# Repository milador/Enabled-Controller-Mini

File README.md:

# Enabled-Controller-Mini

Enabled Controller Mini is a more affordable version of <a href="https://github.com/milador/Enabled-Controller">Enabled-Controller</a> which is an open-source switch controller interface that enables those with limited or no hand movement to use Adaptive switches as input to operate and perform joystick actions.

The device offers up to four switch input enclosures through four 3.5mm audio jacks and two analog inputs through one 3.5mm headphone jack. The one 3.5mm headphone jacks can be used to connect one X-Y analog joystick.

The internal RGB led of QT Py board is used to provide visual feedback for each action.

## Assembly Instructions Manual

The <a href="https://github.com/milador/Enabled-Controller-Mini/blob/main/Documentation/Build_Manuals/Enabled_Controller_Mini_Instructions_Manual.pdf">Assembly Instructions Manual</a> is available to download.

## Parts

The <a href="https://github.com/milador/Enabled-Controller-Mini/blob/main/Components/Enabled_Controller_Mini_BOM.csv">BOM</a> file is available to download.

## Software

The first experimental software is under testing.

## Hardware 

### PCB Design 

The <a href="https://github.com/milador/Enabled-Controller-Mini/tree/main/Hardware/PCB">PCB files</a> including both PCB Eagle design files and generated gerber files are available to download.

### Enclosure

The <a href="https://github.com/milador/Enabled-Controller-Mini/tree/main/Hardware/Enclosure">Enclosure files</a> including both STL and STEP enclosure files are available to download.

## License

### Creative Commons Attribution-NonCommercial-ShareAlike (CC-BY-NC-SA)

Copyright (c) 2021 Milador

A creative commons license that bans commercial use and requires you to release any modified works under this license.

<br />This work is licensed under a <a rel="license" href="http://creativecommons.org/licenses/by-nc-sa/3.0/">Creative Commons Attribution-NonCommercial-ShareAlike 3.0 Unported License</a>.

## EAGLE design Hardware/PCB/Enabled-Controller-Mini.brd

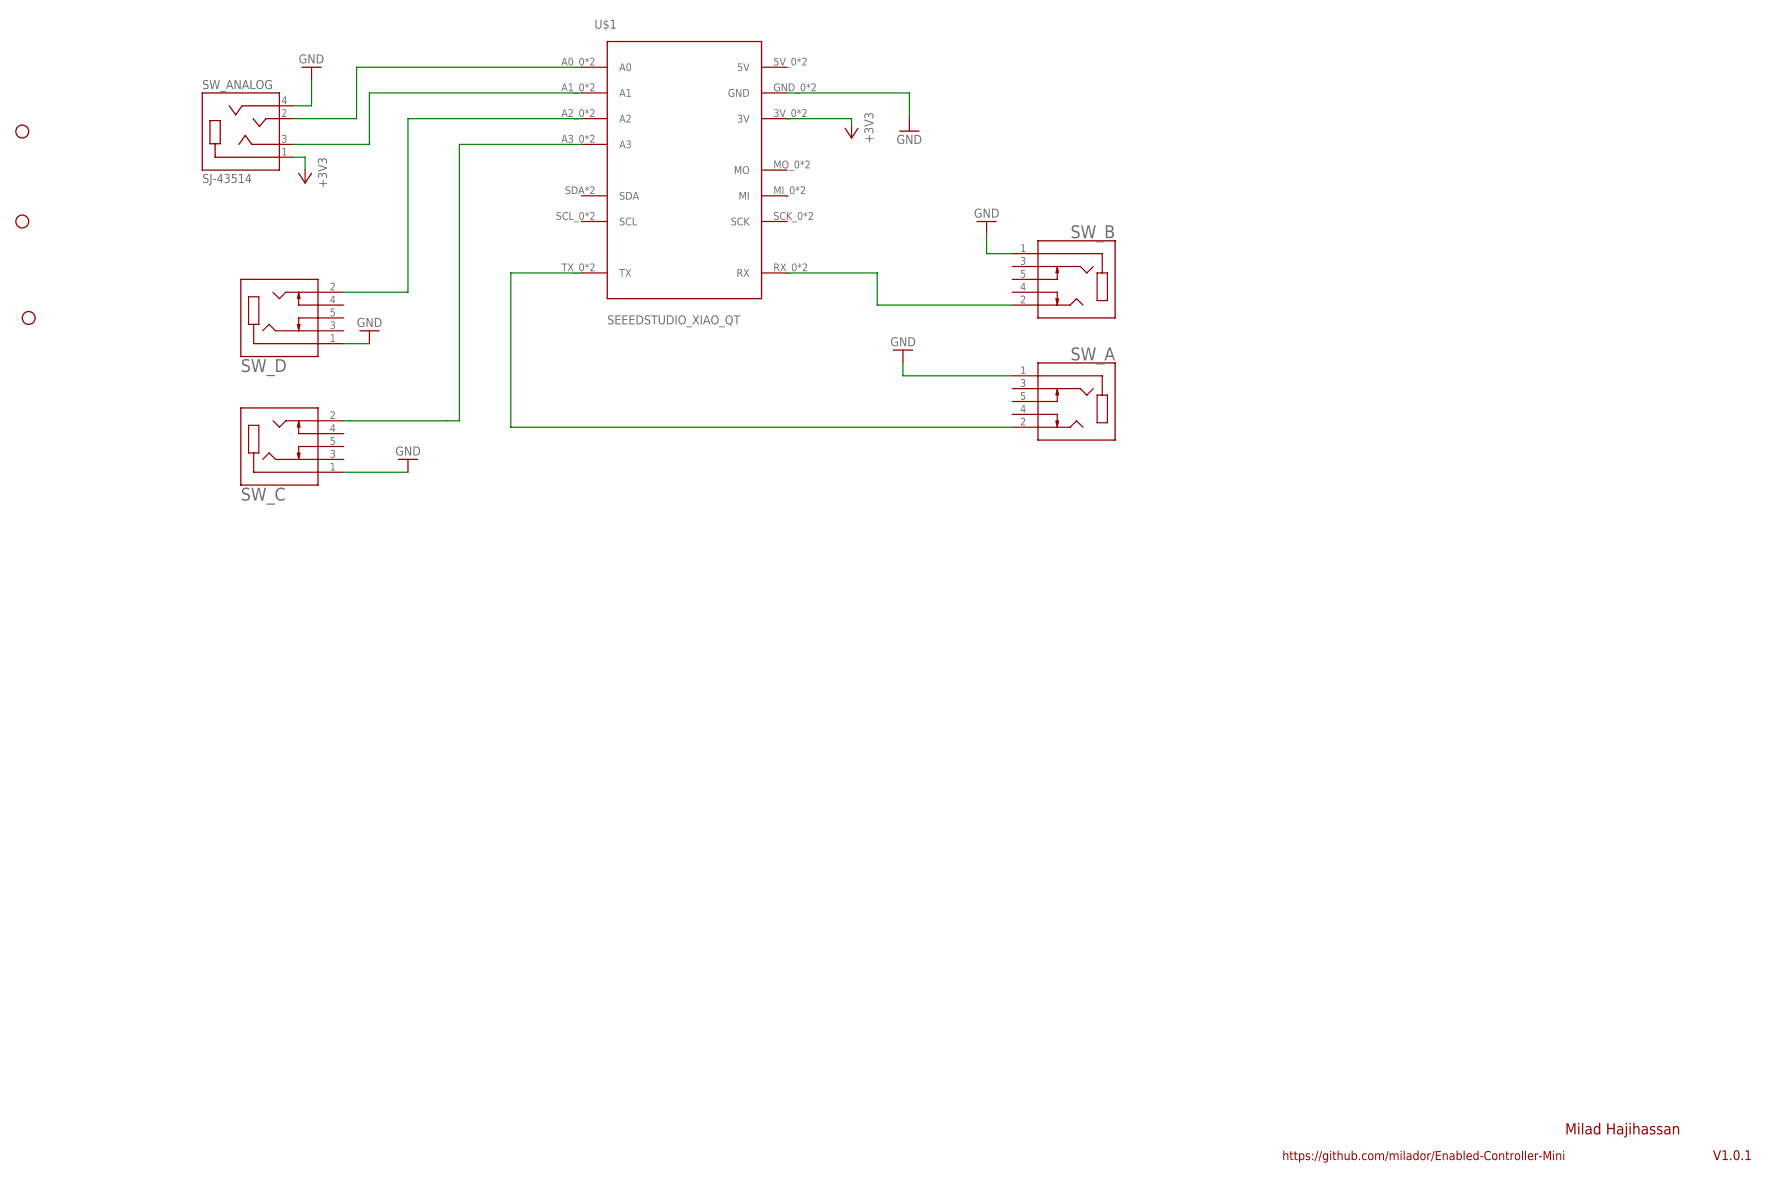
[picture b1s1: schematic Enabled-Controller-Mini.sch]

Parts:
STANDOFF1, STANDOFF2, STANDOFF3: STAND-OFF-; STAND-OFF
SW_A: CUI_SJ1-3535NGSJ1-3535NG; CUI_SJ1-3535NG
SW_ANALOG: SJ-43514; CUI_SJ-43514
SW_B: CUI_SJ1-3535NGSJ1-3535NG; CUI_SJ1-3535NG
SW_C: CUI_SJ1-3535NGSJ1-3535NG; CUI_SJ1-3535NG
SW_D: CUI_SJ1-3535NGSJ1-3535NG; CUI_SJ1-3535NG
U$1: SEEEDSTUDIO_XIAO_QT; SEEEDSTUDIO_XIAO

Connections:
+3V3: SW_ANALOG.1 (SLEEVE), U$1.3V_0 (3V), U$1.3V_1 (3V)
GND: SW_A.1, SW_ANALOG.4 (RING2), SW_B.1, SW_C.1, SW_D.1, U$1.GND_0 (GND), U$1.GND_1 (GND)
unnamed: SW_B.2, U$1.RX_0 (RX), U$1.RX_1 (RX)
unnamed: SW_A.2, U$1.TX_0 (TX), U$1.TX_1 (TX)
unnamed: SW_ANALOG.2 (TIP), U$1.A0_0 (A0), U$1.A0_1 (A0)
unnamed: SW_C.2, U$1.A3_0 (A3), U$1.A3_1 (A3)
unnamed: SW_ANALOG.3 (RING1), U$1.A1_0 (A1), U$1.A1_1 (A1)
unnamed: SW_D.2, U$1.A2_0 (A2), U$1.A2_1 (A2)

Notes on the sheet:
V1.0.1
Milad Hajihassan
https://github.com/milador/Enabled-Controller-Mini

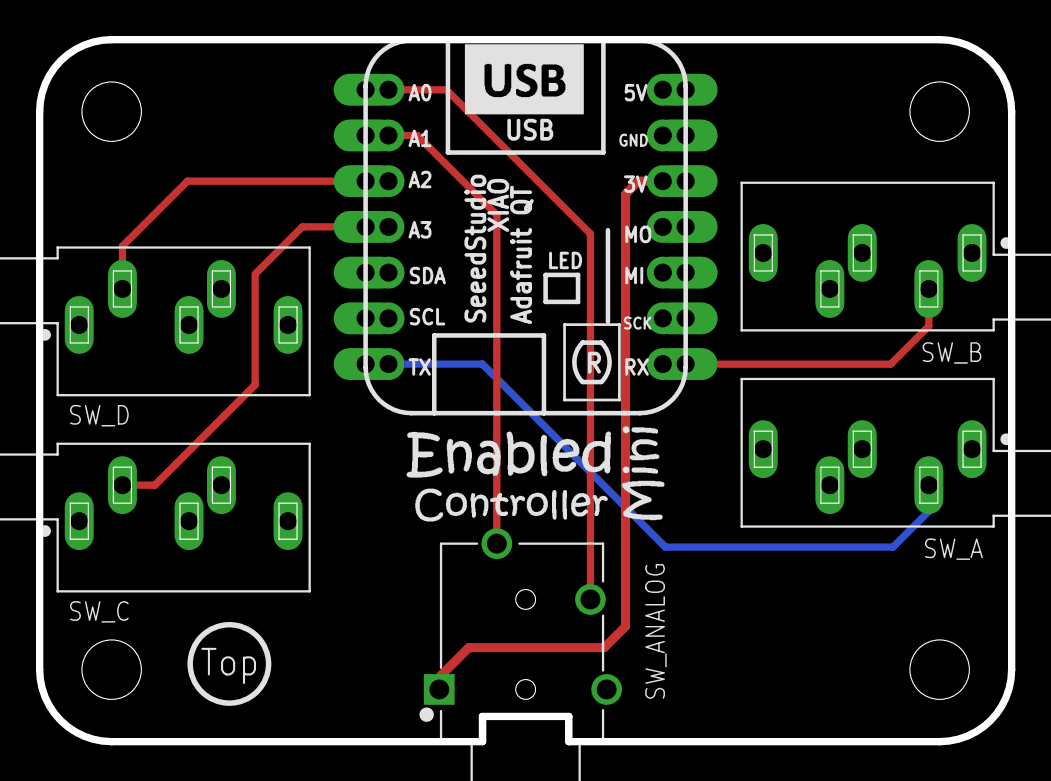
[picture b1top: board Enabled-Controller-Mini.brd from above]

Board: 2 copper layers, 54.0 x 39.0 mm, 10 parts (0 on the bottom side), 8 nets.

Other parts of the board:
STANDOFF44: STAND-OFF-; STAND-OFF

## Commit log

2021-01-17 Updated Enclosure : Snap wall height was increased by 0.8mm.
2021-01-18 Added BOM file
2021-01-18 Added Assembly Instructions Manual
2021-01-18 Added PCB Eagle design files and gerber files
2021-01-18 Added the new images
2021-01-18 Added information about the project
2021-01-21 Updated PCB design files : SWITCH GPIO's changed to A0,A1,A2,A3
2021-01-21 Updated Gerber files : Version 1.1
2021-01-21 Beta software for testing
2021-01-23 Reversed PCB design file
2021-01-23 Added experimental software
2021-01-23 Updated STEP files
2021-01-24 Tested code in Seeedstudio XAIO
2021-01-25 Added USB User Manual
2021-01-25 Added OS Profile selection option
2021-01-31 Updated Assembly manual 1.11
2021-01-31 Tested Arduino code: Basis functionality
2021-01-31 Corrected flag
2021-02-01 Corrected links
2021-02-01 Corrected switch pins
2021-02-01 Added CP code
2021-02-01 Corrected default values
2021-02-01 Added CP readme
2021-02-01 Added CircuitPython software setup
2021-02-01 Updated text
2021-02-26 Added license
2021-02-26 Update LICENSE
2021-02-26 Updated CP code
2021-04-07 Corrected uf2 link
2021-04-10 Added joystick user Manual
2021-08-21 Updated the top enclosure
2021-11-03 Added CircuitPython uf2 files
2021-11-03 Moved uf2 files
2021-11-03 Updated CircuitPython readme
2022-04-09 Update to resolve the else if bug
2022-04-16 Updated the software : OS Profile change
2022-09-17 Added media consumer option
2023-02-13 Added Mouse Mover firmware (Tash)
2023-06-06 Added XAC joystick compatible software
2023-06-06 Updated image
2023-06-29 Update Version 1.3
    Updated Enclosure and assembly guide

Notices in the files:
parts and their libraries:
SparkFun-Aesthetics: Licensing: Creative Commons ShareAlike 4.0 International - https://creativecommons.org/licenses/by-sa/4.0
